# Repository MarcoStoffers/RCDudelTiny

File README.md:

# RCDudelTiny
## MP3-Player control via RC

- This board will control the following functions of a MP3-Player: ON / OFF | Play / Pause | Next / Previous | Volume + / -
- The functions will be controlled by only one RC channel. See my Youtube Video of my prototype for a short intro: https://youtu.be/fYEXbu7Ohzc

## Requirement
- A MP3-Player or MP3-board with 3.3 to 5.5V Power
- An amplifier with 1W - 50W regarding the used speaker
- Power supply for amplifier (the MP3-Player will be powered via the RC Receiver

## Connection
Have a look at the following pinout of the MP3-Player connector. A detailed Manual is also available (only german at this time) with lots of informations for building the RCDudelTiny and disassembling the MP3-Player

## 2 versions
There are two different Arduino Sketches in there: RCDudelTiny.ino is for a disassembled MP3-Player shown in the manual | RCDudelTiny-board.ino is for these ready MP3-boards including a 1W amplifier.
## Base
The module is based on a microchip ATtiny84A which is programmed via the [Arduino IDE](https://arduino.cc/). To use the microcontroller, the extension of [Spence Konde](https://github.com/SpenceKonde/ATTinyCore) is necessary. Programming is done without a bootloader directly via the ISP connector with an AVR programmer.

## License
The project is licensed under the Creative Common License. A rebuild for private or non-profit associations is desired, commercial rebuild or distribution I forbid. If someone should develop the mixer further, I ask for the naming of the original project.

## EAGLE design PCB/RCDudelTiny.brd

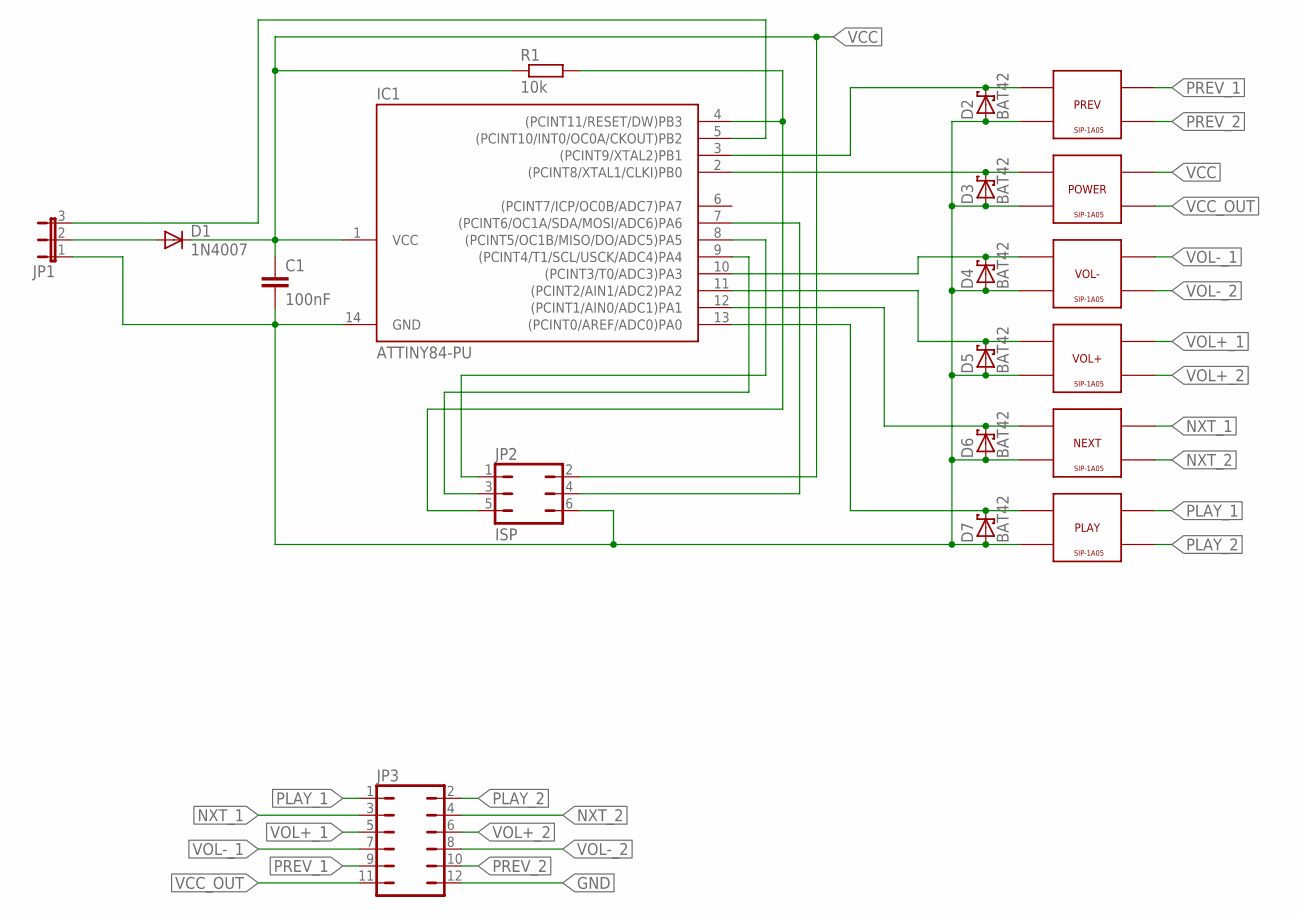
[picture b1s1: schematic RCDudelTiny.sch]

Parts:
C1: 100nF; C025-025X050
D1: 1N4007; DO41-10
D2, D3, D4, D5, D6, D7: BAT42; DO35-10
IC1: ATTINY84-PU; DIL14
JP1: JP2EJP2_OHNE_TEXT; JP2
JP2: ISP; JP3Q
JP3: JP6Q
NEXT: SIP1A05
PLAY: SIP1A05
POWER: SIP1A05
PREV: SIP1A05
R1: 10k; 0207/7
VOL+: SIP1A05
VOL-: SIP1A05

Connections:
GND: C1.2, D2.A, D3.A, D4.A, D5.A, D6.A, D7.A, IC1.14 (GND), JP1.1, JP2.6, JP3.12, NEXT.SP2, PLAY.SP2, POWER.SP2, PREV.SP2, VOL+.SP2, VOL-.SP2
unnamed: D1.A, JP1.2
unnamed: IC1.5 ((PCINT10/INT0/OC0A/CKOUT)PB2), JP1.3
unnamed: IC1.4 ((PCINT11/RESET/DW)PB3), JP2.5, R1.2
unnamed: IC1.8 ((PCINT5/OC1B/MISO/DO/ADC5)PA5), JP2.1
unnamed: IC1.9 ((PCINT4/T1/SCL/USCK/ADC4)PA4), JP2.3
unnamed: IC1.7 ((PCINT6/OC1A/SDA/MOSI/ADC6)PA6), JP2.4
unnamed: D2.C, IC1.3 ((PCINT9/XTAL2)PB1), PREV.SP1
unnamed: D3.C, IC1.2 ((PCINT8/XTAL1/CLKI)PB0), POWER.SP1
unnamed: D4.C, IC1.10 ((PCINT3/T0/ADC3)PA3), VOL-.SP1
unnamed: D5.C, IC1.11 ((PCINT2/AIN1/ADC2)PA2), VOL+.SP1
unnamed: D6.C, IC1.12 ((PCINT1/AIN0/ADC1)PA1), NEXT.SP1
unnamed: D7.C, IC1.13 ((PCINT0/AREF/ADC0)PA0), PLAY.SP1
NXT_1: JP3.3, NEXT.K1
NXT_2: JP3.4, NEXT.K2
PLAY_1: JP3.1, PLAY.K1
PLAY_2: JP3.2, PLAY.K2
PREV_1: JP3.9, PREV.K1
PREV_2: JP3.10, PREV.K2
VCC: C1.1, D1.C, IC1.1 (VCC), JP2.2, POWER.K1, R1.1
VCC_OUT: JP3.11, POWER.K2
VOL+_1: JP3.5, VOL+.K1
VOL+_2: JP3.6, VOL+.K2
VOL-_1: JP3.7, VOL-.K1
VOL-_2: JP3.8, VOL-.K2

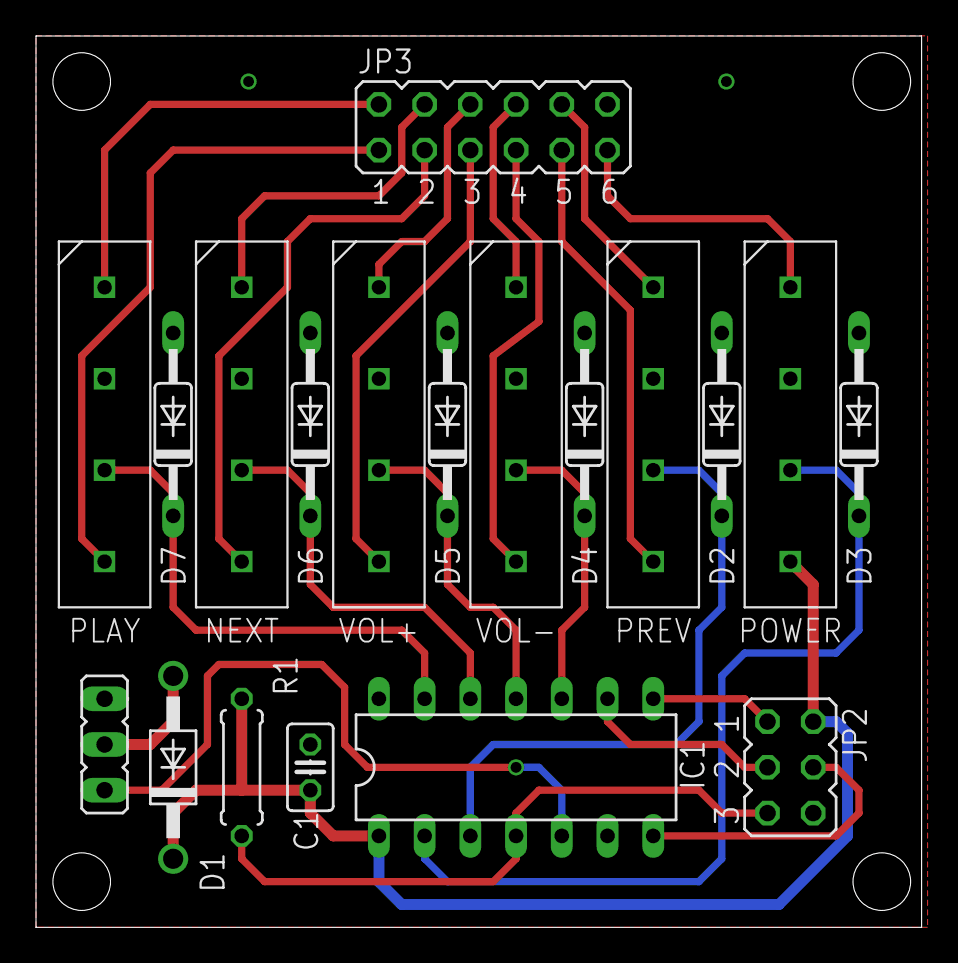
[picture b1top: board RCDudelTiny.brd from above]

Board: 2 copper layers, 49.2 x 49.5 mm, 19 parts (0 on the bottom side), 25 nets.

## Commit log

2019-10-06 New Setup by Jürgen O. for better integration for FlySky transmitter (needs fix position of switches to initialize)
2019-10-11 Add files via upload
    Additional information about the "-board" version
    Output overview for both versions.
2019-10-11 New Setup by Jürgen O. for better integration for FlySky transmitter …
    …(needs fix position of switches to initialize)
    Additional Information in Header About Version.
